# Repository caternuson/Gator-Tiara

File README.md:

# Gator-Tiara
Eagle PCB files for alligator clip to breadboard.

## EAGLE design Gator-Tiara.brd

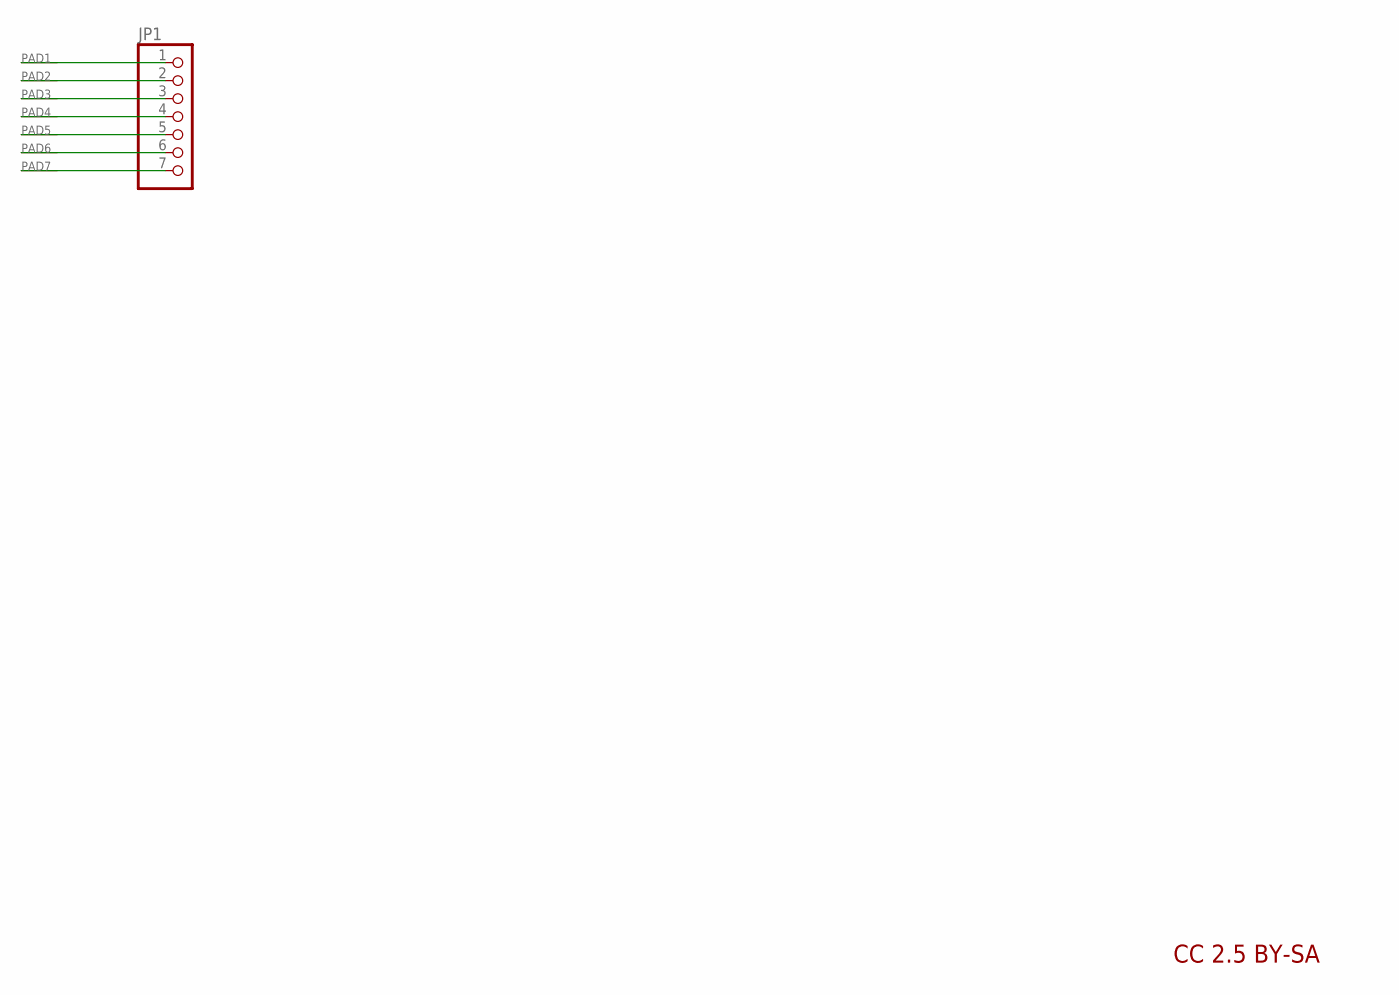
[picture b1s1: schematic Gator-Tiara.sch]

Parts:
JP1: PINHD-1X7/90; 1X07/90
PAD1, PAD2, PAD3, PAD4, PAD5, PAD6, PAD7: SEWTAP-ALLIGATOR; SEWALLI

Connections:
unnamed: JP1.1, PAD1.P$1
unnamed: JP1.2, PAD2.P$1
unnamed: JP1.3, PAD3.P$1
unnamed: JP1.4, PAD4.P$1
unnamed: JP1.5, PAD5.P$1
unnamed: JP1.6, PAD6.P$1
unnamed: JP1.7, PAD7.P$1

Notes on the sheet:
CC 2.5 BY-SA

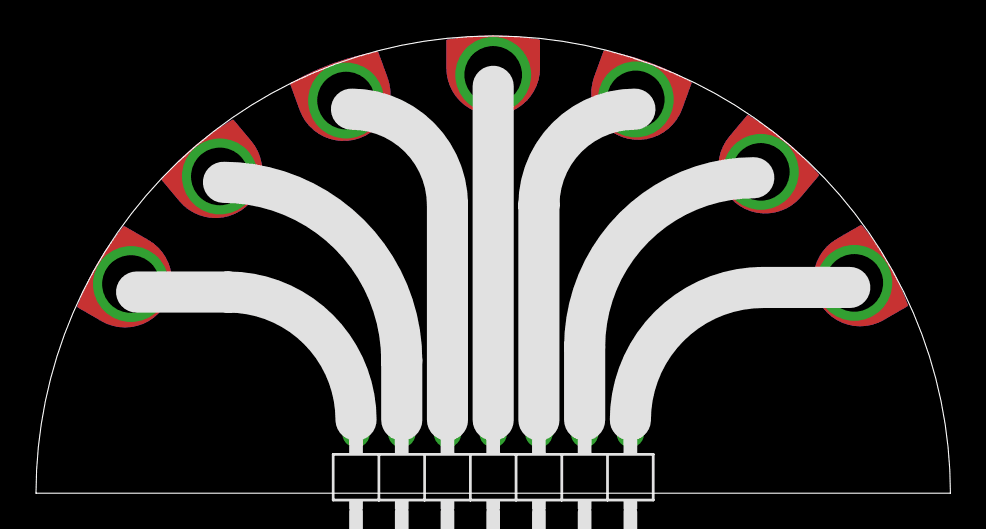
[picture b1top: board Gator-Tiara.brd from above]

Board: 2 copper layers, 50.8 x 25.4 mm, 8 parts (0 on the bottom side), 7 nets.

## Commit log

2017-04-19 adding files

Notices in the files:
parts and their libraries:
microbuilder: This work is placed in the public domain, and may be freely used for commercial and non-commercial work with the following conditions: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
